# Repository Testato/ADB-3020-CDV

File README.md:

# ADB-3020-CDV

The ADB-3020 is an excellent switching power supply designed by an Italian team and licensed under Creative Commons (the original project and credits are in the adb_2030_Original subfolder).

The CDV (Community Digital Version) fork is intended to start with version 2.1 (last published on the fork date) and then extend it with digital functions via MCU.
The project started with the creation of Eagle .sch because the original authors have decided not to release the productions files. 
Now Eagle file is deprecated, the project is ported on KiCAD.

The CDV version is released under the same license as the original project:
- https://creativecommons.org/licenses/by-nc-sa/4.0/

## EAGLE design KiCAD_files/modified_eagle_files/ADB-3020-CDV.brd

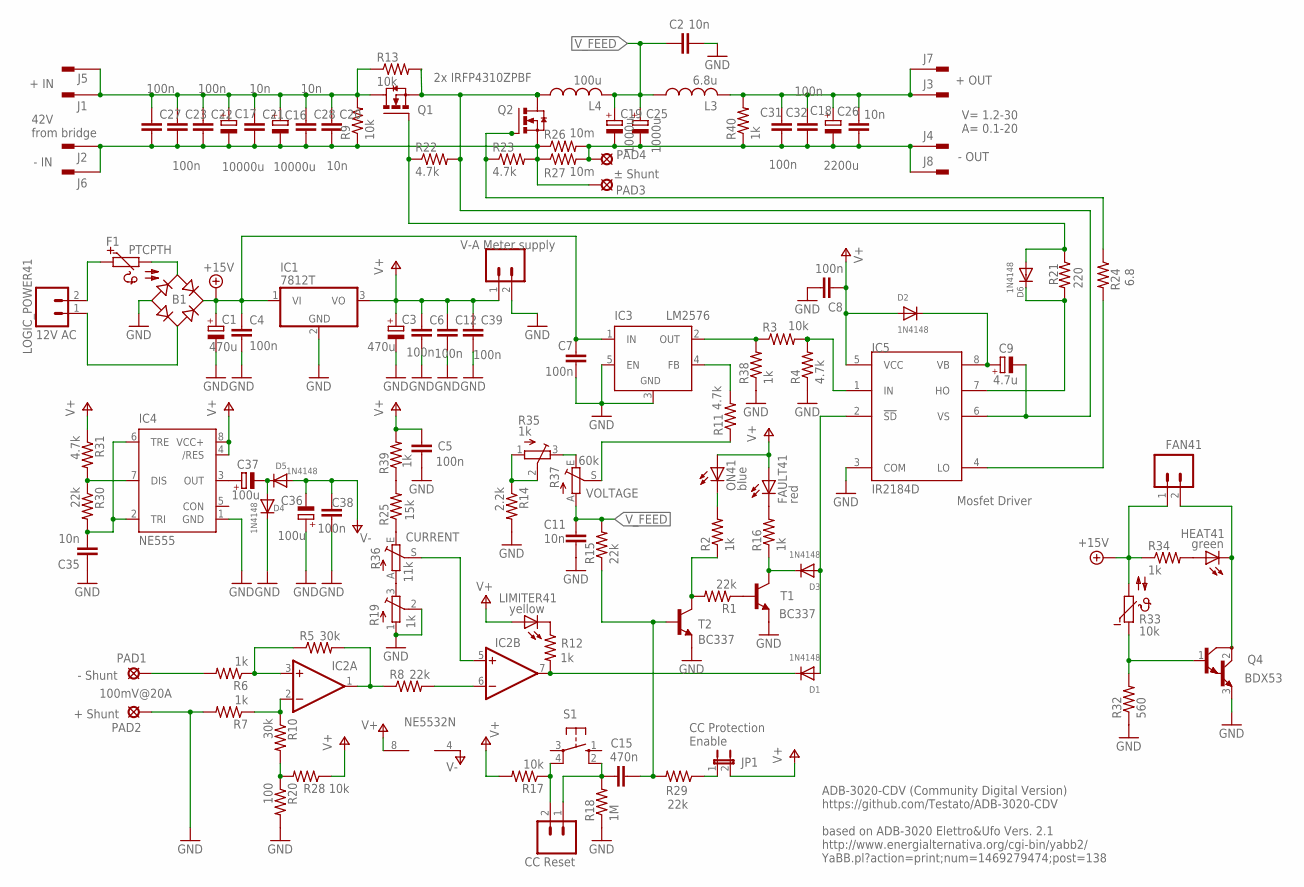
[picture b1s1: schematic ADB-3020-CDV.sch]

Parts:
B1: RECTIFIER-RB1A; RB1A
C1, C3: 470u; E2-5
C2, C11, C20, C21, C26, C28, C35: 10n; C2.5-2
C4, C5, C6, C7, C8, C12, C22, C23, C27, C31, C32, C38, C39: 100n; C2.5-2
C9: 4.7u; E2-5
C15: 470n; C2.5-2
C16, C17: 10000u; E2-5
C18: 2200u; E2-5
C19, C25: 1000u; E2-5
C36, C37: 100u; E2-5
D1, D2, D3, D4, D5, D6: 1N4148; DO-1N4148
F1: PTCPTH; P660
FAN41: fan; 02PA
FAULT41: red; LED3MM
HEAT41: green; LED3MM
IC1: 7812T; TO220H
IC2: NE5532N; DIL08
IC3: LM2576; TO220-52
IC4: NE555; DIL-08
IC5: IR2184D; DIL08
J1, J5: + IN; F061.040
J2, J6: - IN; F061.040
J3: + OUT; F061.040
J4, J7: PIN2F061.040; F061.040
J8: - OUT; F061.040
JP1: jp1; JP1
L3: 6.8u; 6000
L4: 100u; 6000
LIMITER41: yellow; LED3MM
LOGIC_POWER41: 12V AC; 02PA
ON41: blue; LED3MM
PAD1, PAD2, PAD3, PAD4: LSP13
Q1, Q2: IRFP240-H; TO247BH
Q4: BDX53; TO220
R1, R8, R15, R29, R30: 22k; 0204/5
R2, R6, R7, R12, R16, R34, R38, R39, R40: 1k; 0204/5
R3, R9, R13, R17, R28: 10k; 0204/5
R4, R11, R22, R23, R31: 4.7k; 0204/5
R5, R10: 30k; 0204/5
R14: 2.2k; 0204/5
R18: 1M; 0204/5
R19, R35: 1k; TRIM-3386
R20: 100; 0204/5
R21: 220; 0204/5
R24: 6.8; 0204/5
R25: 15k; 0204/5
R26, R27: 10m; 0204/5
R32: 560; 0204/5
R33: 10k; P640
R36: 11k; S64YW
R37: 60k; S64YW
RESET41: CC Reset; 02PA
S1: CC Reset; B3F-40XX
T1, T2: BC337; TO92
V-A_METER_SUPPLY41: V-A Meter supply; 02PA

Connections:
+15V: B1.+, C1.+, C4.1, C7.1, FAN41.1, IC1.1 (VI), IC3.1 (IN), R33.2, R34.1
GND: B1.-, C1.-, C2.2, C3.-, C4.2, C5.1, C6.2, C7.2, C8.2, C11.2, C12.2, C35.1, C36.+, C38.1, C39.2, D4.C, IC1.2 (GND), IC3.3 (GND), IC3.5 (EN), IC4.1 (GND), IC5.3 (COM), PAD2.MP, Q4.3 (E), R4.1, R7.2, R14.2, R18.1, R19.1 (A), R19.2 (S), R20.2, R32.1, R38.1, T1.1 (E), T2.1 (E), V-A_METER_SUPPLY41.2
unnamed: B1.AC2, LOGIC_POWER41.1
unnamed: B1.AC1, F1.2
unnamed: F1.1, LOGIC_POWER41.2
unnamed: D6.A, Q1.G, R21.1, R22.1
unnamed: IC5.1 (IN), R3.2, R4.2
unnamed: IC2.6 (-IN), R8.2
unnamed: IC3.4 (FB), R11.2
unnamed: IC3.2 (OUT), R3.1, R38.2
unnamed: JP1.1, R29.1
unnamed: C37.+, IC4.3 (OUT)
unnamed: C37.-, D4.A, D5.C
unnamed: R25.2, R39.1
unnamed: FAULT41.K (C), R16.2
unnamed: R10.2, R20.1, R28.2
unnamed: ON41.K (C), R2.2
unnamed: LIMITER41.K (C), R12.1
unnamed: R1.1, T1.2 (B)
unnamed: IC4.7 (DIS), R30.1, R31.2
unnamed: C35.2, IC4.2 (TRI), IC4.6 (TRE), R30.2
unnamed: R25.1, R36.E
unnamed: R19.3 (E), R36.A
unnamed: IC2.5 (+IN), R36.S
unnamed: IC2.1 (OUT), R5.2, R8.1
unnamed: IC2.3 (+IN), R5.1, R6.1
unnamed: IC2.2 (-IN), R7.1, R10.1
unnamed: PAD1.MP, R6.2
unnamed: R17.1, RESET41.2, S1.4 (P1)
unnamed: C15.1, R18.2, RESET41.1, S1.2 (S1)
unnamed: C15.2, R15.1, R29.2, T2.2 (B)
unnamed: D1.C, IC2.7 (OUT), R12.2
unnamed: R14.1, R35.1 (A), R35.2 (S)
unnamed: R35.3 (E), R37.E
unnamed: R1.2, R2.1, T2.3 (C)
unnamed: R11.1, R37.S
unnamed: D3.C, R16.1, T1.3 (C)
unnamed: D1.A, D3.A, IC5.2 (!SD)
unnamed: C18.-, C19.-, C25.-, C26.2, C31.2, C32.2, J4.A1, J4.A2, J8.A1, J8.A2, PAD4.MP, R26.2, R27.2, R40.1
unnamed: D6.C, IC5.7 (HO), R21.2
unnamed: C16.+, C17.+, C20.1, C21.1, C22.1, C23.1, C27.1, C28.1, J1.A1, J1.A2, J5.A1, J5.A2, Q1.D, R9.2, R13.1
unnamed: IC5.4 (LO), R24.2
unnamed: Q2.G, R23.1, R24.1
unnamed: HEAT41.A, R34.2
unnamed: FAN41.2, HEAT41.K (C), Q4.2 (C)
unnamed: Q4.1 (B), R32.2, R33.1
unnamed: C16.-, C17.-, C20.2, C21.2, C22.2, C23.2, C27.2, C28.2, J2.A1, J2.A2, J6.A1, J6.A2, PAD3.MP, Q2.S, R9.1, R23.2, R26.1, R27.1
unnamed: C18.+, C26.1, C31.1, C32.1, J3.A1, J3.A2, J7.A1, J7.A2, L3.2, R40.2
V+: C3.+, C5.2, C6.1, C8.1, C12.1, C39.1, D2.A, FAULT41.A, IC1.3 (VO), IC2.8 (V+), IC4.4 (/RES), IC4.8 (VCC+), IC5.5 (VCC), JP1.2, LIMITER41.A, ON41.A, R17.2, R28.1, R31.1, R39.2, V-A_METER_SUPPLY41.1
V-: C36.-, C38.2, D5.A, IC2.4 (V-)
VB: C9.+, D2.C, IC5.8 (VB)
VS: C9.-, IC5.6 (VS), L4.1, Q1.S, Q2.D, R13.2, R22.2
V_FEED: C2.1, C11.1, C19.+, C25.+, L3.1, L4.2, R15.2, R37.A

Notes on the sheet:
2x IRFP4310ZPBF
100mV@20A
- Shunt
+ Shunt
± Shunt
ADB-3020-CDV (Community Digital Version) https://github.com/Testato/ADB-3020-CDV based on ADB-3020 Elettro&Ufo Vers. 2.1 http://www.energialternativa.org/cgi-bin/yabb2/ YaBB.pl?action=print;num=1469279474;post=138
42V from bridge
V= 1.2-30 A= 0.1-20
CURRENT
VOLTAGE
CC Protection Enable
Mosfet Driver

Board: 2 copper layers, 113 parts (0 on the bottom side), 53 nets, no tracks yet.

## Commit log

2017-05-27 Update README.md
    The license name was wrong (https://github.com/Testato/ADB-3020-CDV/issues/1)
2017-05-27 added ne5532 supply pins
2017-05-28 Complete boom included external components
2017-05-28 info added
2017-05-30 Added components values, reviewed some connections
    Waiting for a review before merge
2017-05-31 Fixed component designators
    Fixed components designators to match those in the original schematic and bom
2017-05-31 Fixed some connections
2017-06-02 Create LICENSE
2017-06-02 Rename LICENSE to LICENSE.md
2017-06-02 Grid 0,1" + some component name corrections
2017-06-03 removed unused joint connection + minor graphic change
2017-08-26 Added footprints
    To do before merge:
    * review the footprints
    * draw inductors footprints
    * draw J1 to J8 footprints (faston tabs)
2017-08-26 first KiCAD version whit sch and pcb
2017-08-27 Almost finished layout and fixes.
    * fixed fp-lib-table
    * fixed schematic
    Missing:
    * faston footprints
    * faston in layout
    Requires review
2017-08-29 Completed layout
    * added last footprints
    * added silkscreen wordings
    * adedd logos
    * added soldermask zones
    * fixed component identifier positions
    Missing:
2017-08-29 Completed the layout
2017-08-30 Removed all ERC, repaired annotation on sch and pcb, added sheet pcb info, revisited .sch component name value position
2018-01-30 Creato .gitattributes

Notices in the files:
README.md:
License: CC BY-NC-SA 4.0
